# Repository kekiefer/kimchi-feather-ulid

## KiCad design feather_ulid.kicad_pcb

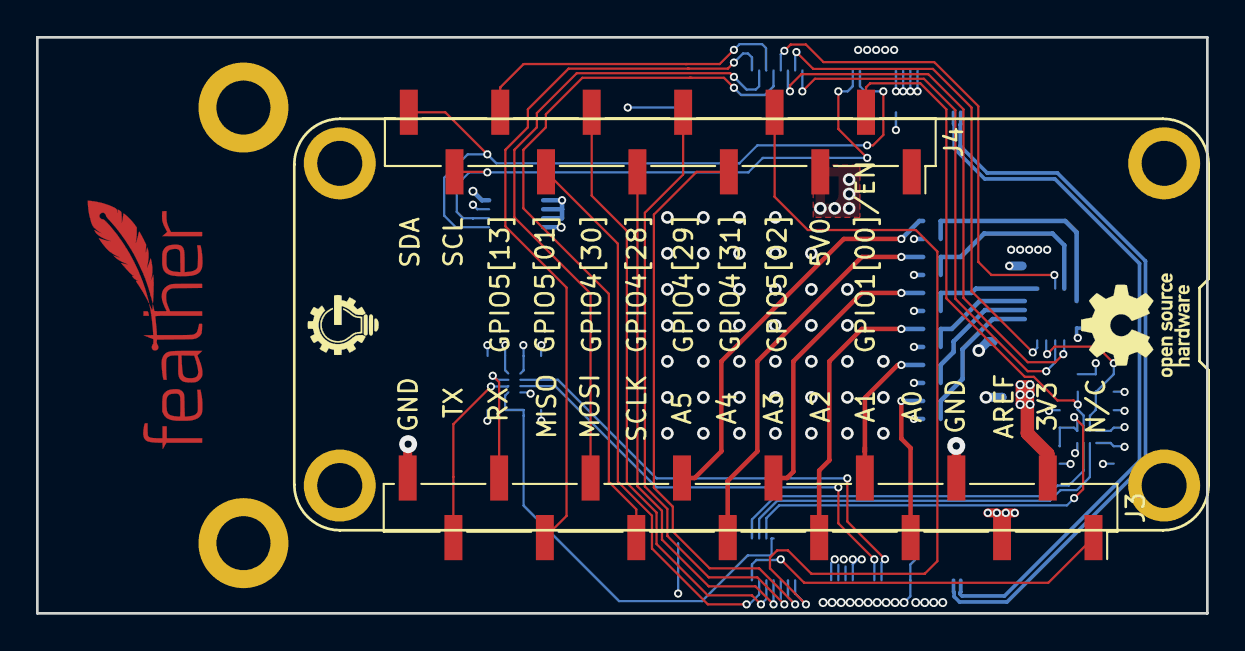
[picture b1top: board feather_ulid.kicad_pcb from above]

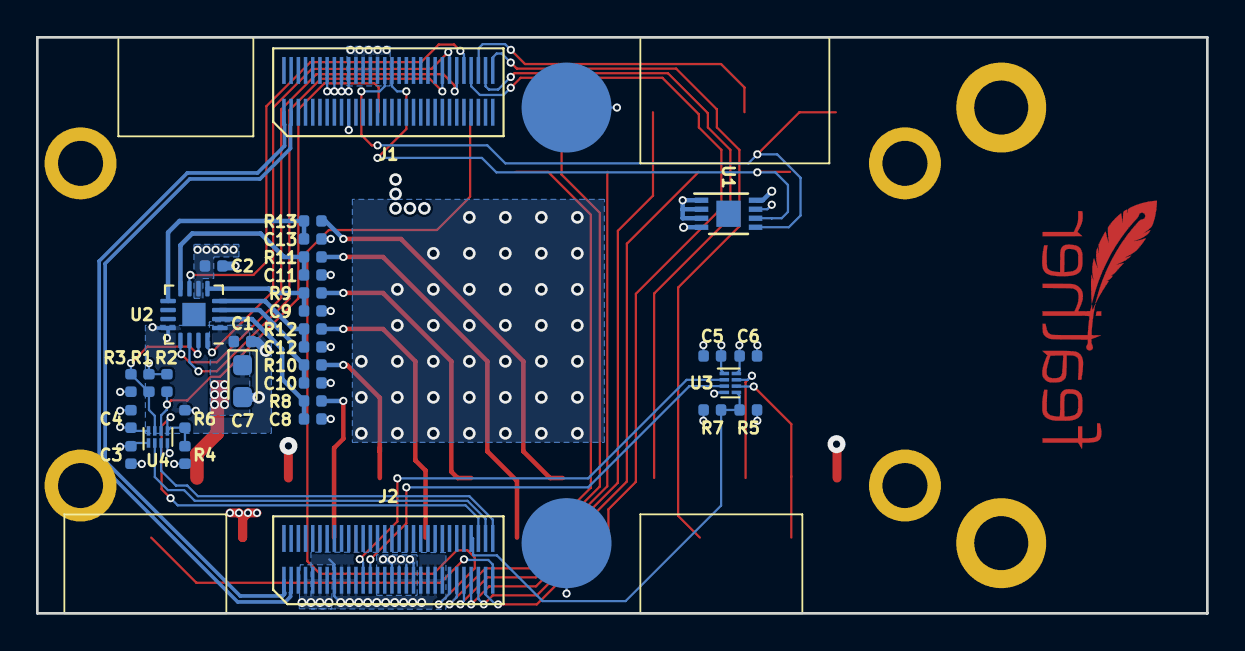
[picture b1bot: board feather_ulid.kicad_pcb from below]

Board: 4 copper layers, 65.0 x 32.0 mm, 45 parts (34 on the bottom side), 46 nets.

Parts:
C1, C2, C3, C4, C5, C6: 0.1uF; C_0402_1005Metric
C7: CP_Small; CP_EIA-2012-15_AVX-P
C8, C9, C10, C11, C12, C13: 680pF 1%; C_0402_1005Metric
FID1: Fiducial; Untitled
H1, H2, H3, H4: MountingHole_Pad; MountingHole_3mm_Pad
H5, H6, H7, H8: MountingHole_Pad; MountingHole_2.5mm_Pad
J1, J2: DF40HC(3.5)-60DS
J3: Conn_Left; PinHeader_1x16_P2.54mm_Vertical_SMD_Pin1Right
J4: Conn_Right; PinHeader_1x12_P2.54mm_Vertical_SMD_Pin1Right
L1: GG_LOGO; gg-4x4
LOGO1: Logo_Open_Hardware_Small; OSHW-Logo_5.7x6mm_SilkScreen
R1, R2, R3, R4, R5, R6, R7: 100K; R_0402_1005Metric
R8, R9, R10, R11, R12, R13: 12K 1%; R_0402_1005Metric
U1: 24C32; DFN-8-1EP_3x2mm_P0.5mm_EP1.36x1.46mm
U2: AD5592R; LFCSP-16-1EP_3x3mm_P0.5mm_EP1.3x1.3mm
U3, U4: TXS0102DQE; X2SON-8_1.4x1mm_P0.35mm

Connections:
/A0: J3.5, R8.2
/A0_F: C8.1, R8.1, U2.2
/A1: J3.6, R10.2
/A1_F: C10.1, R10.1, U2.3
/A2: J3.7, R12.2
/A2_F: C12.1, R12.1, U2.4
/A3: J3.8, R9.2
/A3_F: C9.1, R9.1, U2.5
/A4: J3.9, R11.2
/A4_F: C11.1, R11.1, U2.8
/A5: J3.10, R13.2
/A5_F: C13.1, R13.1, U2.9
/Aref: C2.1, J3.3, U2.6
/EN: J4.2, R2.2, U4.6
/GPIO1[1]_HV: R1.2, R3.1, U2.15, U4.7
/RX: J3.14, U3.7
/TX: J3.15, U3.6
ECSPI1_MISO: J1.26, U2.7
ECSPI1_MOSI: J1.25, U2.13
ECSPI1_SCLK: J1.23, U2.14
ECSPI1_SS0: J1.24, U2.16
ECSPI2_MISO: J1.30, J3.13
ECSPI2_MOSI: J1.29, J3.12
ECSPI2_SCLK: J1.27, J3.11
ECSPI2_SS0: J1.28, J4.10
GND: C1.1, C2.2, C3.2, C4.2, C5.2, C6.2, C7.2, C8.2, C9.2, C10.2, C11.2, C12.2, C13.2, H1.1, H2.1, H3.1, H4.1, H5.1, H6.1, H7.1, J1.11, J1.12, J1.13, J1.14, J1.51, J2.38, J2.39, J2.40, J2.41, J2.50, J2.51, J2.52, J2.53, J3.4, J3.16, R3.2, R6.2, R7.2, U1.4, U1.7, U2.12, U3.4, U4.4
GPIO1[0]: J2.30, U4.3
GPIO1[1]: J2.29, U4.2
GPIO1[9]: J2.28, R4.2, R6.1, U4.5
GPIO1[10]: J2.27, R5.2, R7.1, U3.5
I2C4_SCL: J1.16, J4.11, U1.6
I2C4_SDA: J1.15, J4.12, U1.5
PCIE_USB_D_N: J1.59, J2.60
PCIE_USB_D_P: J1.60, J2.59
SAI3_MCLK: J2.37, J4.4
SAI3_RXC: J2.35, J4.6
SAI3_RXD: J2.33, J4.8
SAI3_RXFS: J2.34, J4.7
SAI3_TXC: J2.31, J3.1
SAI3_TXD: J2.32, J4.9
SAI3_TXFS: J2.36, J4.5
UART3_RX: J2.49, U3.2
UART3_TX: J2.48, U3.3
VDD_1V8: C3.1, C5.1, J2.42, J2.43, J2.44, J2.45, R4.1, R5.1, U3.1, U4.1
VDD_3V3: C1.2, C4.1, C6.1, C7.1, J2.54, J2.55, J2.56, J2.57, J3.2, R1.1, R2.1, U1.1, U1.2, U1.3, U1.8, U2.1, U3.8, U4.8
VDD_5V: J1.7, J1.8, J1.9, J1.10, J4.3

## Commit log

2020-11-30 Create feature ulid project
